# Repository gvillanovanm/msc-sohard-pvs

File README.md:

## SOHARD-PVS: SOftware & HARDware - Pacemaker Verification System

SOHARD-PVS is a platform that allows for easy testing of pacemaker models. It focuses on both the software behavior and electrical circuits of the pacemaker, and the electrical heart characteristics.

In this repository, the pacemaker and heart models used were developed by the University of Pennsylvania. These models are automata-based and are used to represent the software behavior of the pacemaker and the temporization of the cardiac conduction system of the heart. 

In this work, the pacemaker model includes the following electrical circuits:

* battery;
* sensing;
* pacing;
* leads;
* telemetry.

Additionally, the heart model includes the following features:

* electrode-tissue interface;
* depolarization is based on energy transferred to the heart tissue, according to the strength-duration curve.

This extension allows a closed-loop model (heart and pacemaker) considering software and hardware specifications.

### Organization of repository 

#### project/

Pacemaker and heart models implemented with MATLAB Simulink.

#### fpga/

Simulation of simplified automata-based heart model on modelsim software and synthesis of simplified automata-based heart model on DE0-nano-SoC platform.

#### kicad/

Printed Circuit Board to couple real pacemaker and FPGA heart model.

### Papers and others links

#### Papers
* Magalhães, Gabriel VN, Gutemberg G. Santos Jr, and Antonio MN Lima. "An electrical extension of automata-based heart models for closed-loop validation of pacemakers." Simpósio Brasileiro de Automação Inteligente-SBAI. Vol. 1. No. 1. 2021.

#### Links
* [Paper presentation (in Portuguese)](https://www.youtube.com/watch?v=I9eNSNevT-Y&t).
* [Platform presentation (in Portuguese)](https://www.youtube.com/watch?v=zhirvjsvrzc).

### About

This work was developed in the Master's course at the Federal University of Campina Grande - UFCG.

* Embedded and Pervasive Computing Laboratory - [embedded.ufcg.edu.br](embedded.ufcg.edu.br)
* Electrical Engineering Department - DEE - [www.ee.ufcg.edu.br](www.ee.ufcg.edu.br)
* Electrical Engineering and Informatics Center - CEEI
* Federal University of Campina Grande - UFCG - [www.ufcg.edu.br](www.ufcg.edu.br)

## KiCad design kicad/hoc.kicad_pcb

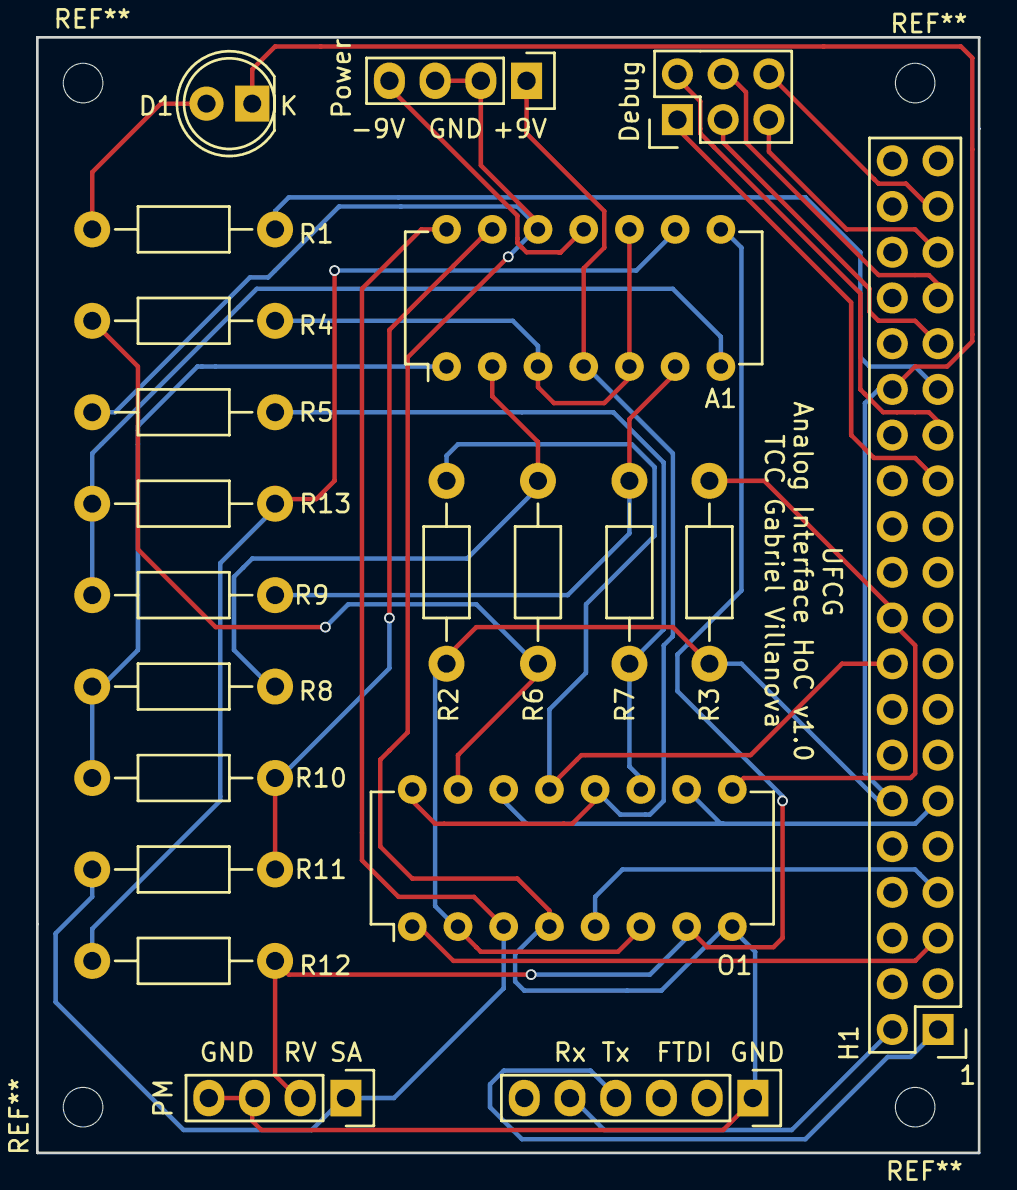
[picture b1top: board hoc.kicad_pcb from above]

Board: 2 copper layers, 52.3 x 62.0 mm, 21 parts (0 on the bottom side), 30 nets.

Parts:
A1: LF347N; DIP-14_W7.62mm
D1: LED; LED-5MM
Debug: CONN_02X03; Pin_Header_Straight_2x03
FTDI: CONN_01X06; Pin_Header_Straight_1x06
H1: CONN_02X20; Pin_Header_Straight_2x20
O1: TLP624-4; DIP-16_W7.62mm
PM: CONN_01X04; Pin_Header_Straight_1x04
Power: CONN_01X04; Pin_Header_Straight_1x04
R1, R2, R3, R4, R5: 330; Resistor_Horizontal_RM10mm
R6, R7: 100k; Resistor_Horizontal_RM10mm
R8, R9: 150; Resistor_Horizontal_RM10mm
R10, R11, R12, R13: 10k; Resistor_Horizontal_RM10mm

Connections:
3V3_FPGA: H1.29, R1.2
5V_FPGA: H1.11, O1.10, O1.14
+9V: A1.4, O1.12, O1.16, Power.1
-9V: A1.11, Power.4
CLOCK_1_5: Debug.2, H1.27
GND: A1.12, FTDI.1, O1.4, O1.8, PM.3, PM.4, Power.2, Power.3, R5.1
GND_FPGA: D1.1, H1.12, H1.30, O1.2, O1.6, R2.2, R3.1
NA1out: Debug.3, H1.31
NA3out: Debug.5, H1.35
unnamed: D1.2, R1.1
unnamed: A1.1, R8.1, R10.2
unnamed: A1.2, R6.1, R8.2
unnamed: A1.6, R7.1, R9.2
unnamed: A1.7, R9.1, R13.2
unnamed: A1.9, R12.1, R13.1
unnamed: A1.3, A1.5, A1.10, R4.2
unnamed: A1.13, R10.1, R11.1
unnamed: O1.11, R5.2, R7.2
unnamed: O1.15, R4.1, R6.2
RA_pace: A1.14, O1.3, PM.1, R11.2
RV_out: H1.7, O1.5
RV_pace: A1.8, O1.7, PM.2, R12.2
SA_out: H1.5, O1.1
apace_in: H1.18, O1.13, R2.1
apace_latch: Debug.4, H1.33
rx_fpga: FTDI.4, H1.1
tx_fpga: FTDI.5, H1.2
tx_go: Debug.1, H1.25
vpace_in: H1.20, O1.9, R3.2
vpace_latch: Debug.6, H1.37

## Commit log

2023-01-20 Update README: add paper
2023-01-29 Update README.md: add video links
2023-07-04 chore: cleans ips_CASE0_normal
2023-07-04 feat: updates gitignore
2023-07-04 chore: removes redundant codes in ips_CASE0_normal.m
2023-07-04 chore: updates code ips_CASE1* to be equal to ips_CASE0*, except the parameters related to SA disfun. condition
2023-07-04 chore: updates code ips_CASE1* and ips_CASE2* to be equal to ips_CASE0*, except the parameters related to heart conditions
2023-07-04 chore: updates code ips_CASE3* to be equal to ips_CASE0*, except the parameters related to heart conditions
